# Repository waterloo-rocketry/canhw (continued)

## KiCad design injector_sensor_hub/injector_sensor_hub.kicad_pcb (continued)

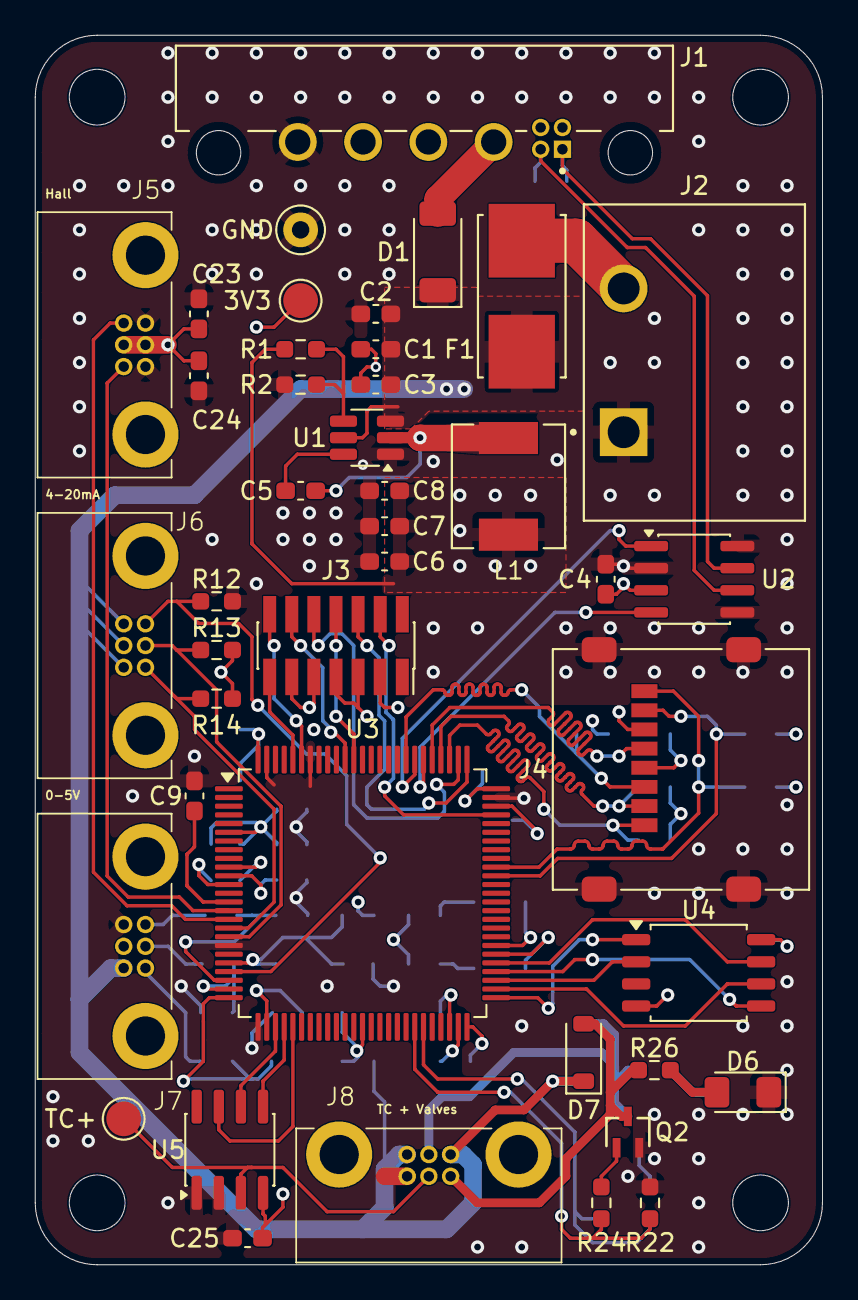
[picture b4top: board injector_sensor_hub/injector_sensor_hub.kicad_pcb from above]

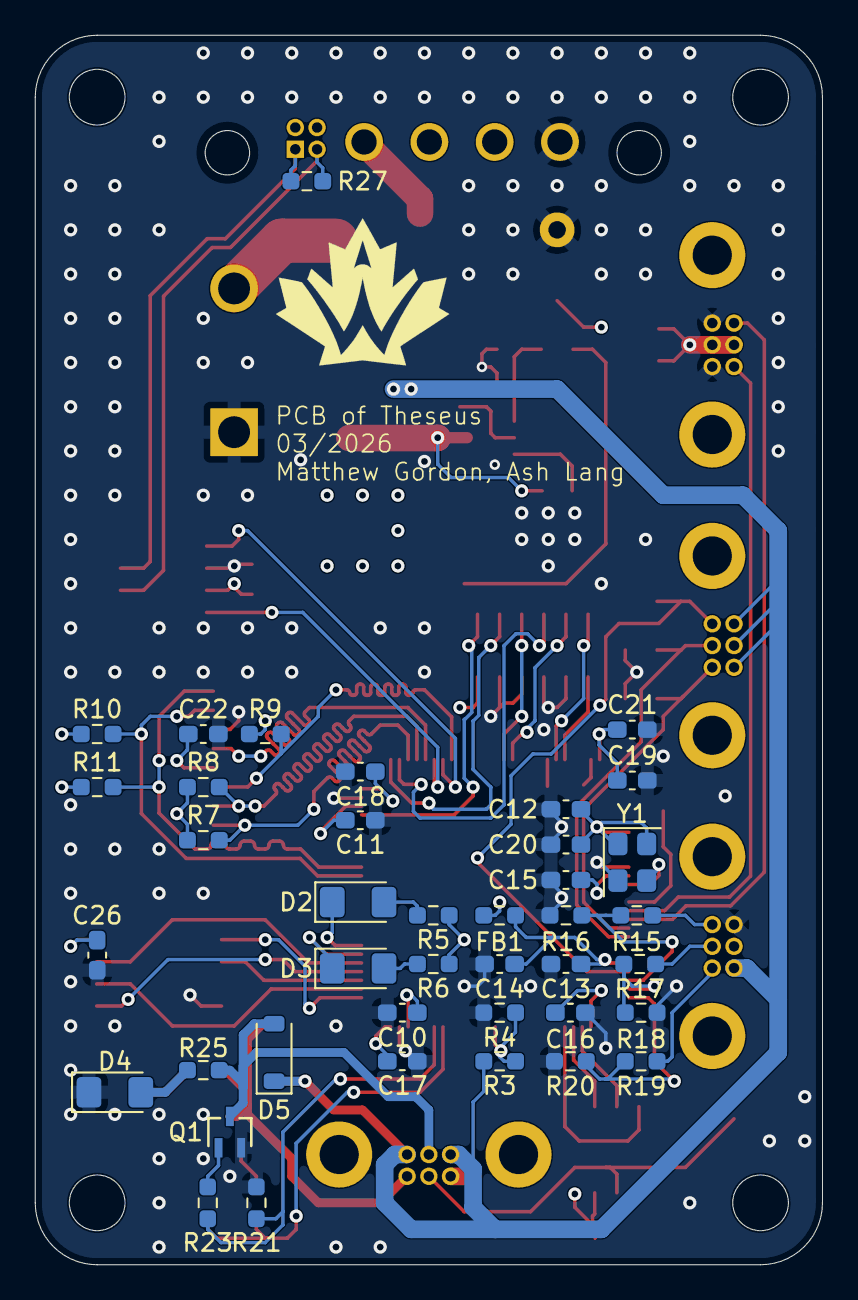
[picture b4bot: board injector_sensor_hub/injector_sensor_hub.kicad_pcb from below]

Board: 4 copper layers, 45.2 x 70.6 mm, 86 parts (40 on the bottom side), 63 nets.

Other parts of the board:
3V3: TestPoint; TestPoint_Pad_D2.0mm
GND: TestPoint; TestPoint_Keystone_5000-5004_Miniature
TC+: TC1+; TestPoint_Pad_D2.0mm

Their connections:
+3.3V: 3V3.1; also elsewhere on the board
/Valves and Sensors/TC1+: TC+.1; also elsewhere on the board
GND: GND.1; also elsewhere on the board

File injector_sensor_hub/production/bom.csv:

Designator,Footprint,Quantity,Value,LCSC Part #
3V3,TestPoint_Pad_D2.0mm,1,TestPoint,
"C1, C2, C22",0603,3,10u,
"C10, C11",0603,2,2.2u,
"C12, C13, C15, C16, C17, C18, C19, C26, C3, C5, C9",0603,11,100n,
C14,0603,1,1n,
C20,0603,1,0.01uF,
C21,0603,1,4.7u,
"C23, C24, C25, C4",0603,4,0.1u,
"C6, C7, C8",0603,3,22u,
D1,D_SOD-128,1,PMEG3030EP,
D2,1206,1,WHITE,
D3,1206,1,BLUE,
"D4, D6",1206,2,GREEN,
"D5, D7",D_SOD-123,2,CDBW140-G,
F1,FUSE_0154005.DR,1,0154005.DRL,
FB1,0603,1,PE-0603PFB121ST,
GND,TestPoint_Keystone_5000-5004_Miniature,1,TestPoint,
J1,connector_Harwin_G125-MH104M4-04AD000P,1,G125-MH104M4-04AD000P,
J2,4DB-P108-02,1,4DB-P108-02,
J3,PinSocket_2x07_P1.27mm_Vertical_SMD,1,CN4 STDC14 (Programmer),
J4,microSD_HC_Molex_47219-2001,1,Micro SD Holder 0472192001,
"J5, J6, J7, J8",connector_Harwin_G125–MG10605M4P,4,Conn_01x06_Socket,
L1,IND_SPM6530T-2R2M,1,SPM6530T-2R2M,
"Q1, Q2",SOT_12UW-7_DIO,2,DMG1012UW-7,
R1,0603,1,33.2k,
"R10, R11, R7, R8, R9",0603,5,51k,
"R12, R13, R14",0603,3,150R ±0.1%,
"R15, R17, R19",0603,3,82K,
"R16, R18, R20",0603,3,130K,
R2,0603,1,10k,
"R21, R22",0603,2,150k,
"R23, R24",0603,2,100R,
"R25, R26",0603,2,649R,
R27,0603,1,120R,
R3,0603,1,300K,
R4,0603,1,100K,
"R5, R6",0603,2,169R,
TC+,TestPoint_Pad_D2.0mm,1,TC1+,
U1,SOT-23-6_Handsoldering,1,TPS565201DDC,
U2,SOIC-8_3.9x4.9mm_P1.27mm,1,TCAN334,
U3,LQFP-100_14x14mm_P0.5mm,1,STM32H750VBTx,
U4,SOIC-8_5.3x5.3mm_P1.27mm,1,MX25L25645G,
U5,SOIC-8_3.9x4.9mm_P1.27mm,1,MAX6675,
Y1,Oscillator_SMD_Abracon_ASE-4Pin_3.2x2.5mm,1,ASE-4.000MHz-L-C-T,

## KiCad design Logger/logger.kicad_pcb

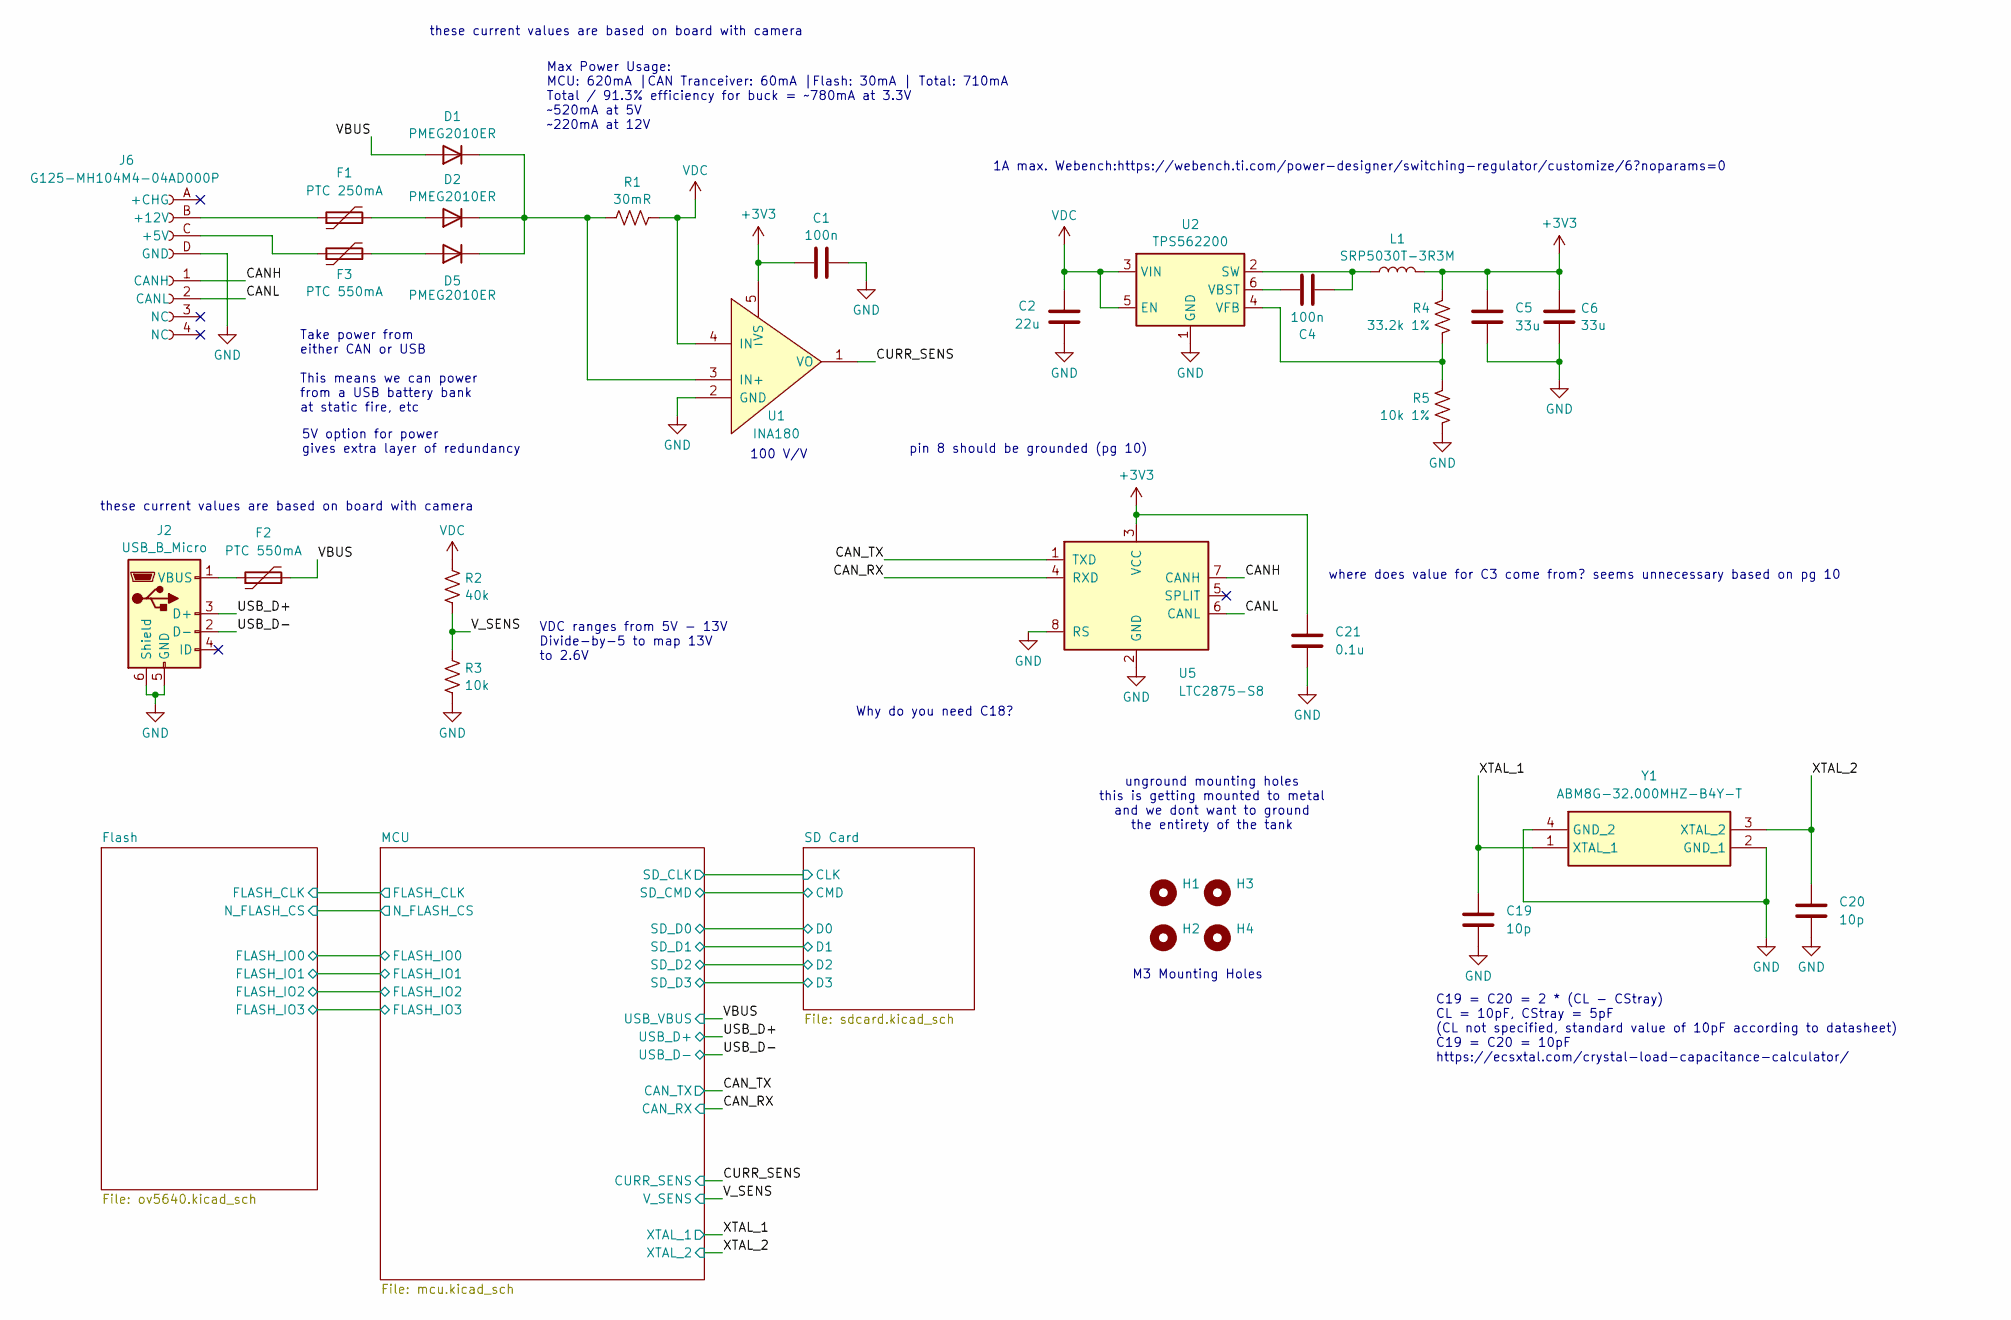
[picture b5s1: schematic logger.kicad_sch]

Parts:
C1, C4: 100n; C_0603_1608Metric_Pad1.08x0.95mm_HandSolder
C2: 22u; C_0603_1608Metric_Pad1.08x0.95mm_HandSolder
C5, C6: 33u; C_0603_1608Metric_Pad1.08x0.95mm_HandSolder
C19, C20: 10p; C_0603_1608Metric_Pad1.08x0.95mm_HandSolder
C21: 0.1u; C_0603_1608Metric_Pad1.08x0.95mm_HandSolder
D1, D2, D5: PMEG2010ER; Nexperia_CFP3_SOD-123W
F1: PTC 250mA; Fuse_1206_3216Metric_Pad1.42x1.75mm_HandSolder
F2, F3: PTC 550mA; Fuse_1206_3216Metric_Pad1.42x1.75mm_HandSolder
H1, H2, H3, H4: MountingHole; MountingHole_3.2mm_M3
J2: USB_B_Micro; USB_Micro-B_Molex_47346-0001
J6: G125-MH104M4-04AD000P; connector_Harwin_G125-MH104M4-04AD000P
L1: SRP5030T-3R3M; L_Bourns_SRP5030T
R1: 30mR; R_0603_1608Metric_Pad0.98x0.95mm_HandSolder
R2: 40k; R_0603_1608Metric_Pad0.98x0.95mm_HandSolder
R3: 10k; R_0603_1608Metric_Pad0.98x0.95mm_HandSolder
R4: 33.2k 1%; R_0603_1608Metric_Pad0.98x0.95mm_HandSolder
R5: 10k 1%; R_0603_1608Metric_Pad0.98x0.95mm_HandSolder
U1: INA180; SOT-23-5_HandSoldering
U2: TPS562200; SOT-23-6_Handsoldering
U5: LTC2875-S8; SOIC-8_3.9x4.9mm_P1.27mm
Y1: ABM8G-32.000MHZ-B4Y-T; Crystal_SMD_Abracon_ABM8G-4Pin_3.2x2.5mm; Manufacturer_Part_Number ABM8G-32.000MHZ-B4Y-T

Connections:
+3V3: C1.1, C5.1, C6.1, C21.1, L1.2, R4.1, U1.5 (VS), U5.3 (VCC); also elsewhere on the board
/CANH: J6.1 (CANH), U5.7 (CANH)
/CANL: J6.2 (CANL), U5.6 (CANL)
/CAN_RX: U5.4 (RXD); also elsewhere on the board
/CAN_TX: U5.1 (TXD); also elsewhere on the board
/CURR_SENS: U1.1 (VO); also elsewhere on the board
/USB_D+: J2.3 (D+); also elsewhere on the board
/USB_D-: J2.2 (D-); also elsewhere on the board
/VBUS: D1.2 (A), F2.2; also elsewhere on the board
/V_SENS: R2.2, R3.1; also elsewhere on the board
/XTAL_1: C19.1, Y1.1 (XTAL_1); also elsewhere on the board
/XTAL_2: C20.1, Y1.3 (XTAL_2); also elsewhere on the board
GND: C1.2, C2.2, C5.2, C6.2, C19.2, C20.2, C21.2, J2.5 (GND), J2.6 (Shield), J6.D (GND), R3.2, R5.2, U1.2 (GND), U2.1 (GND), U5.2 (GND), U5.8 (RS), Y1.2 (GND_1), Y1.4 (GND_2); also elsewhere on the board
unnamed: D1.1 (K), D2.1 (K), D5.1 (K), R1.1, U1.3 (IN+)
unnamed: D2.2 (A), F1.2
unnamed: D5.2 (A), F3.2
unnamed: F2.1, J2.1 (VBUS)
unnamed: F3.1, J6.C (+5V)
unnamed: F1.1, J6.B (+12V)
unnamed: C4.2, L1.1, U2.2 (SW)
unnamed: C4.1, U2.6 (VBST)
unnamed: R4.2, R5.1, U2.4 (VFB)
VDC: C2.1, R1.2, R2.1, U1.4 (IN-), U2.3 (VIN), U2.5 (EN)

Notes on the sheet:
unground mounting holes this is getting mounted to metal and we dont want to ground the entirety of the tank
5V option for power gives extra layer of redundancy
pin 8 should be grounded (pg 10)
C19 = C20 = 2 * (CL - CStray) CL = 10pF, CStray = 5pF (CL not specified, standard value of 10pF according to datasheet) C19 = C20 = 10pF https://ecsxtal.com/crystal-load-capacitance-calculator/
VDC ranges from 5V - 13V Divide-by-5 to map 13V to 2.6V
these current values are based on board with camera
100 V/V
Why do you need C18?
1A max. Webench:https://webench.ti.com/power-designer/switching-regulator/customize/6?noparams=0
M3 Mounting Holes
Max Power Usage: MCU: 620mA |CAN Tranceiver: 60mA |Flash: 30mA | Total: 710mA Total / 91.3% efficiency for buck = ~780mA at 3.3V ~520mA at 5V ~220mA at 12V
where does value for C3 come from? seems unnecessary based on pg 10
Take power from either CAN or USB This means we can power from a USB battery bank at static fire, etc

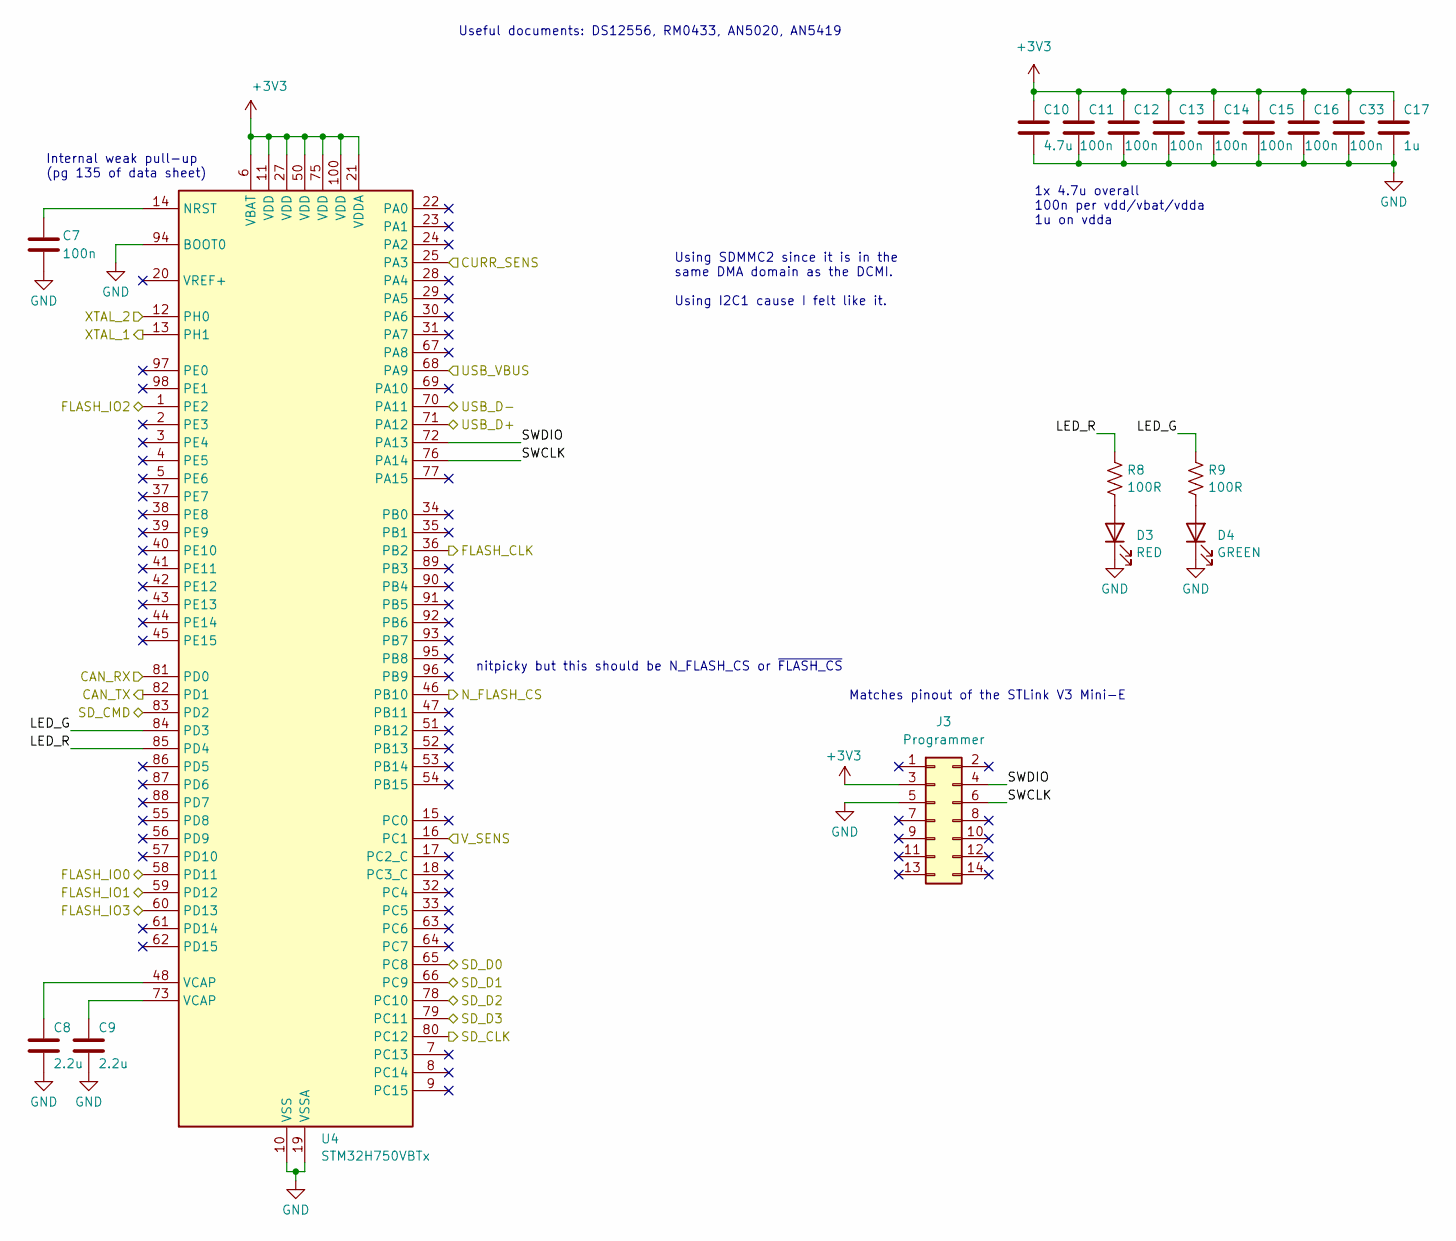
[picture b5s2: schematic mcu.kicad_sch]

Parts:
C7, C11, C12, C13, C14, C15, C16, C33: 100n; C_0603_1608Metric_Pad1.08x0.95mm_HandSolder
C8, C9: 2.2u; C_0603_1608Metric_Pad1.08x0.95mm_HandSolder
C10: 4.7u; C_0603_1608Metric_Pad1.08x0.95mm_HandSolder
C17: 1u; C_0603_1608Metric_Pad1.08x0.95mm_HandSolder
D3: RED; LED_1206_3216Metric_Pad1.42x1.75mm_HandSolder
D4: GREEN; LED_1206_3216Metric_Pad1.42x1.75mm_HandSolder
J3: Programmer; PinHeader_2x07_P1.27mm_Vertical_SMD
R8, R9: 100R; R_0603_1608Metric_Pad0.98x0.95mm_HandSolder
U4: STM32H750VBTx; LQFP-100_14x14mm_P0.5mm

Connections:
+3V3: C10.1, C11.1, C12.1, C13.1, C14.1, C15.1, C16.1, C17.1, C33.1, J3.3, U4.6 (VBAT), U4.11 (VDD), U4.21 (VDDA), U4.27 (VDD), U4.50 (VDD), U4.75 (VDD), U4.100 (VDD); also elsewhere on the board
/CAN_RX: U4.81 (PD0); also elsewhere on the board
/CAN_TX: U4.82 (PD1); also elsewhere on the board
/CURR_SENS: U4.25 (PA3); also elsewhere on the board
/Flash/FLASH_CLK: U4.36 (PB2); also elsewhere on the board
/Flash/FLASH_IO0: U4.58 (PD11); also elsewhere on the board
/Flash/FLASH_IO1: U4.59 (PD12); also elsewhere on the board
/Flash/FLASH_IO2: U4.1 (PE2); also elsewhere on the board
/Flash/FLASH_IO3: U4.60 (PD13); also elsewhere on the board
/Flash/N_FLASH_CS: U4.46 (PB10); also elsewhere on the board
/MCU/LED_G: R9.1, U4.84 (PD3)
/MCU/LED_R: R8.1, U4.85 (PD4)
/MCU/SD_CLK: U4.80 (PC12); also elsewhere on the board
/MCU/SD_CMD: U4.83 (PD2); also elsewhere on the board
/MCU/SD_D0: U4.65 (PC8); also elsewhere on the board
/MCU/SD_D1: U4.66 (PC9); also elsewhere on the board
/MCU/SD_D2: U4.78 (PC10); also elsewhere on the board
/MCU/SD_D3: U4.79 (PC11); also elsewhere on the board
/MCU/SWCLK: J3.6, U4.76 (PA14)
/MCU/SWDIO: J3.4, U4.72 (PA13)
/USB_D+: U4.71 (PA12); also elsewhere on the board
/USB_D-: U4.70 (PA11); also elsewhere on the board
/VBUS: U4.68 (PA9); also elsewhere on the board
/V_SENS: U4.16 (PC1); also elsewhere on the board
/XTAL_1: U4.13 (PH1); also elsewhere on the board
/XTAL_2: U4.12 (PH0); also elsewhere on the board
GND: C7.2, C8.2, C9.2, C10.2, C11.2, C12.2, C13.2, C14.2, C15.2, C16.2, C17.2, C33.2, D3.1 (K), D4.1 (K), J3.5, U4.10 (VSS), U4.19 (VSSA), U4.26 (VSS), U4.49 (VSS), U4.74 (VSS), U4.94 (BOOT0), U4.99 (VSS); also elsewhere on the board
unnamed: C8.1, U4.48 (VCAP)
unnamed: C9.1, U4.73 (VCAP)
unnamed: D3.2 (A), R8.2
unnamed: D4.2 (A), R9.2
unnamed: C7.1, U4.14 (NRST)

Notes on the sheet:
nitpicky but this should be N_FLASH_CS or ~{FLASH_CS}
1x 4.7u overall 100n per vdd/vbat/vdda 1u on vdda
Matches pinout of the STLink V3 Mini-E
Useful documents: DS12556, RM0433, AN5020, AN5419
Using SDMMC2 since it is in the same DMA domain as the DCMI. Using I2C1 cause I felt like it.
Internal weak pull-up (pg 135 of data sheet)

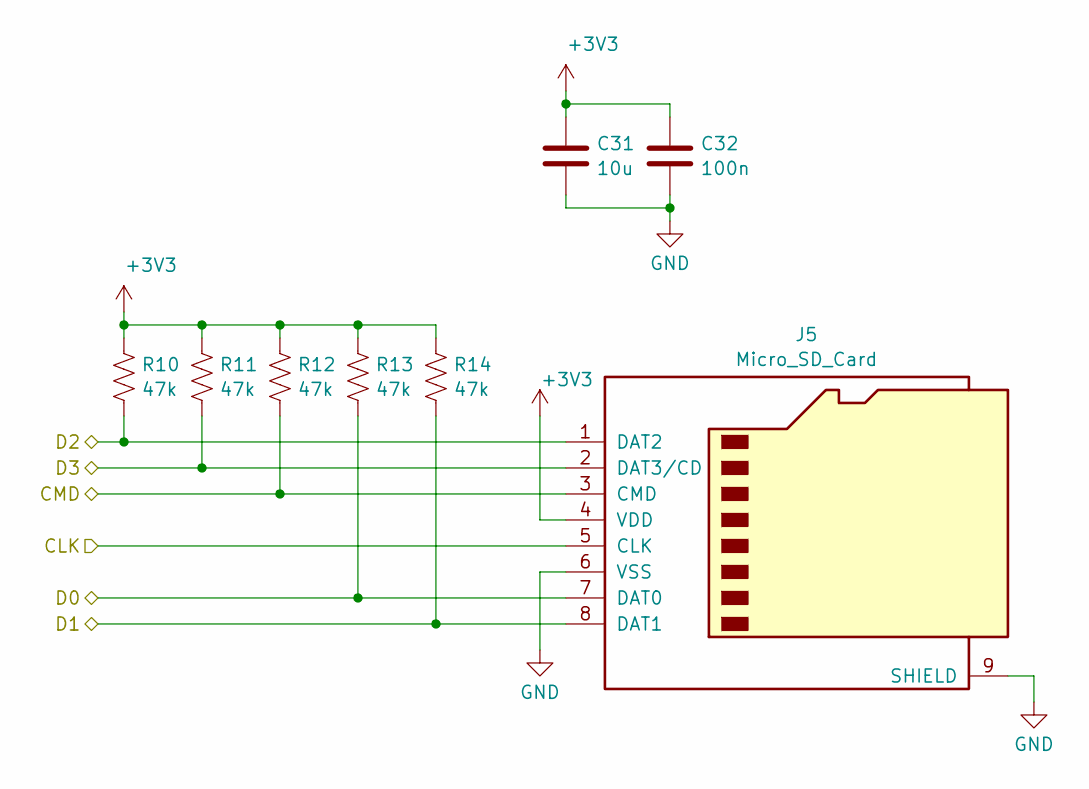
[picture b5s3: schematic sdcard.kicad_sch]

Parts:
C31: 10u; C_0603_1608Metric_Pad1.08x0.95mm_HandSolder
C32: 100n; C_0603_1608Metric_Pad1.08x0.95mm_HandSolder
J5: Micro_SD_Card; microSD_Molex_WM6698CT-ND
R10, R11, R12, R13, R14: 47k; R_0603_1608Metric_Pad0.98x0.95mm_HandSolder

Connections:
+3V3: C31.1, C32.1, J5.4 (VDD), R10.1, R11.1, R12.1, R13.1, R14.1; also elsewhere on the board
/MCU/SD_CLK: J5.5 (CLK); also elsewhere on the board
/MCU/SD_CMD: J5.3 (CMD), R12.2; also elsewhere on the board
/MCU/SD_D0: J5.7 (DAT0), R13.2; also elsewhere on the board
/MCU/SD_D1: J5.8 (DAT1), R14.2; also elsewhere on the board
/MCU/SD_D2: J5.1 (DAT2), R10.2; also elsewhere on the board
/MCU/SD_D3: J5.2 (DAT3/CD), R11.2; also elsewhere on the board
GND: C31.2, C32.2, J5.6 (VSS), J5.9 (SHIELD); also elsewhere on the board

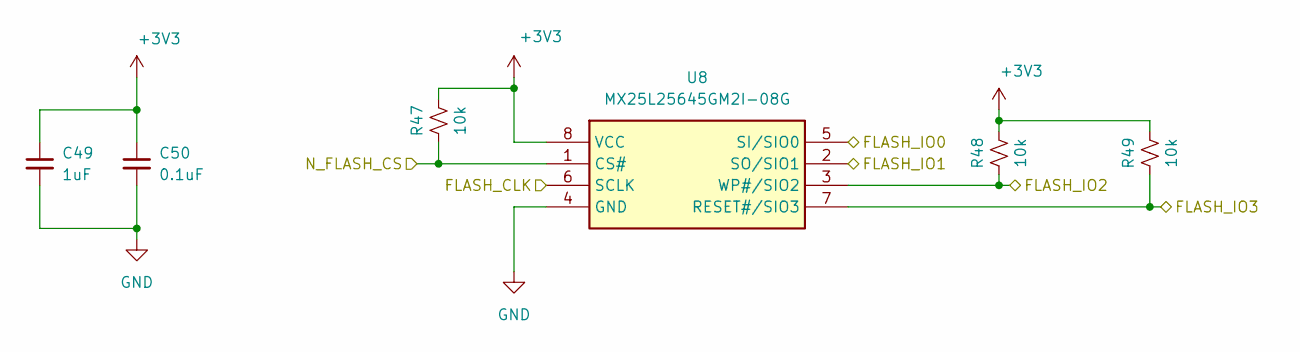
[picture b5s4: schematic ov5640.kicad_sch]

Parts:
C49: 1uF; C_0603_1608Metric_Pad1.08x0.95mm_HandSolder; LCSC Part # C49678
C50: 0.1uF; C_0603_1608Metric_Pad1.08x0.95mm_HandSolder; LCSC Part # C49678
R47, R48, R49: 10k; R_0603_1608Metric_Pad0.98x0.95mm_HandSolder; LCSC Part # C17414
U8: MX25L25645GM2I-08G; SOIC-8_5.3x5.3mm_P1.27mm; Mouser Part Number 95-25L25645GM2I0TR

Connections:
+3V3: C49.1, C50.1, R47.1, R48.1, R49.1, U8.8 (VCC); also elsewhere on the board
/Flash/FLASH_CLK: U8.6 (SCLK); also elsewhere on the board
/Flash/FLASH_IO0: U8.5 (SI/SIO0); also elsewhere on the board
/Flash/FLASH_IO1: U8.2 (SO/SIO1); also elsewhere on the board
/Flash/FLASH_IO2: R48.2, U8.3 (WP#/SIO2); also elsewhere on the board
/Flash/FLASH_IO3: R49.2, U8.7 (RESET#/SIO3); also elsewhere on the board
/Flash/N_FLASH_CS: R47.2, U8.1 (CS#); also elsewhere on the board
GND: C49.2, C50.2, U8.4 (GND); also elsewhere on the board

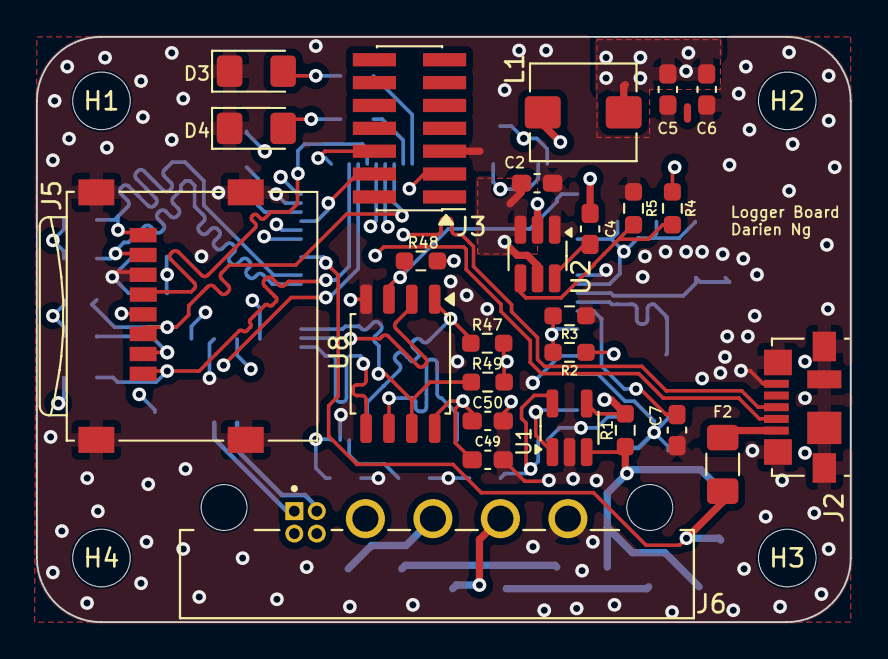
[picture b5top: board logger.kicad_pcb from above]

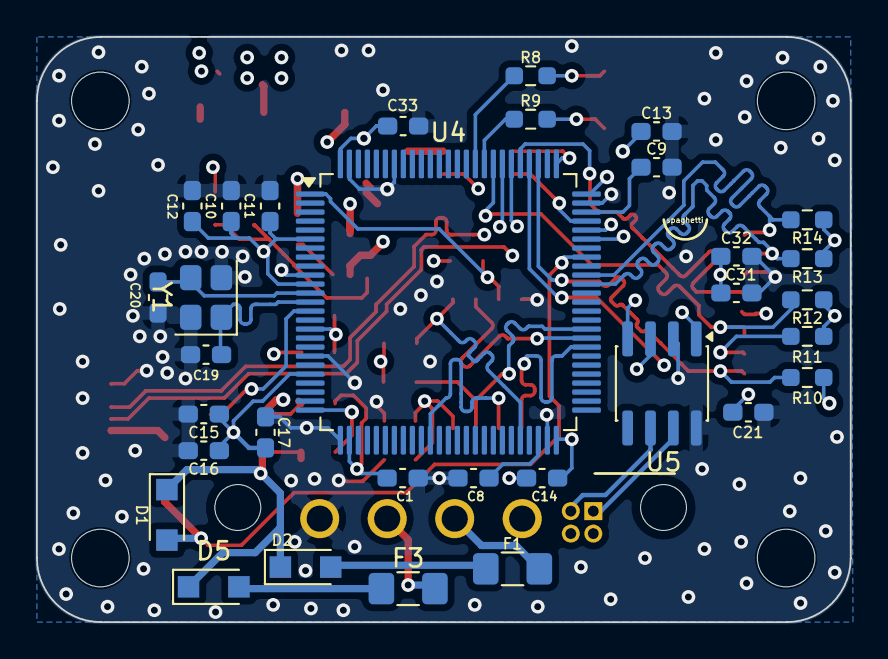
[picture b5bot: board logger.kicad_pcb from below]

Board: 4 copper layers, 45.2 x 32.5 mm, 62 parts (32 on the bottom side), 44 nets.

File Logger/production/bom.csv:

Designator,Footprint,Quantity,Value,LCSC Part #
"C1, C11, C12, C13, C14, C15, C16, C32, C33, C4, C7",0603,11,100n,
C10,0603,1,4.7u,
C17,0603,1,1u,
"C19, C20",0603,2,10p,
C2,0603,1,22u,
C21,0603,1,0.1u,
C31,0603,1,10u,
C49,0603,1,1uF,C49678
"C5, C6",0603,2,33u,
C50,0603,1,0.1uF,C49678
"C8, C9",0603,2,2.2u,
"D1, D2, D5",Nexperia_CFP3_SOD-123W,3,PMEG2010ER,
D3,1206,1,RED,
D4,1206,1,GREEN,
F1,1206,1,PTC 250mA,
"F2, F3",1206,2,PTC 550mA,
J2,USB_Micro-B_Molex_47346-0001,1,USB_B_Micro,
J3,PinHeader_2x07_P1.27mm_Vertical_SMD,1,Programmer,
J5,microSD_Molex_WM6698CT-ND,1,Micro_SD_Card,
J6,connector_Harwin_G125-MH104M4-04AD000P,1,G125-MH104M4-04AD000P,
L1,L_Bourns_SRP5030T,1,SRP5030T-3R3M,
R1,0603,1,30mR,
"R10, R11, R12, R13, R14",0603,5,47k,
R2,0603,1,40k,
R3,0603,1,10k,
R4,0603,1,33.2k 1%,
"R47, R48, R49",0603,3,10k,C17414
R5,0603,1,10k 1%,
"R8, R9",0603,2,100R,
U1,SOT-23-5_HandSoldering,1,INA180,
U2,SOT-23-6_Handsoldering,1,TPS562200,
U4,LQFP-100_14x14mm_P0.5mm,1,STM32H750VBTx,
U5,SOIC-8_3.9x4.9mm_P1.27mm,1,LTC2875-S8,
U8,SOIC-8_5.3x5.3mm_P1.27mm,1,MX25L25645GM2I-08G,
Y1,Crystal_SMD_Abracon_ABM8G-4Pin_3.2x2.5mm,1,ABM8G-32.000MHZ-B4Y-T,

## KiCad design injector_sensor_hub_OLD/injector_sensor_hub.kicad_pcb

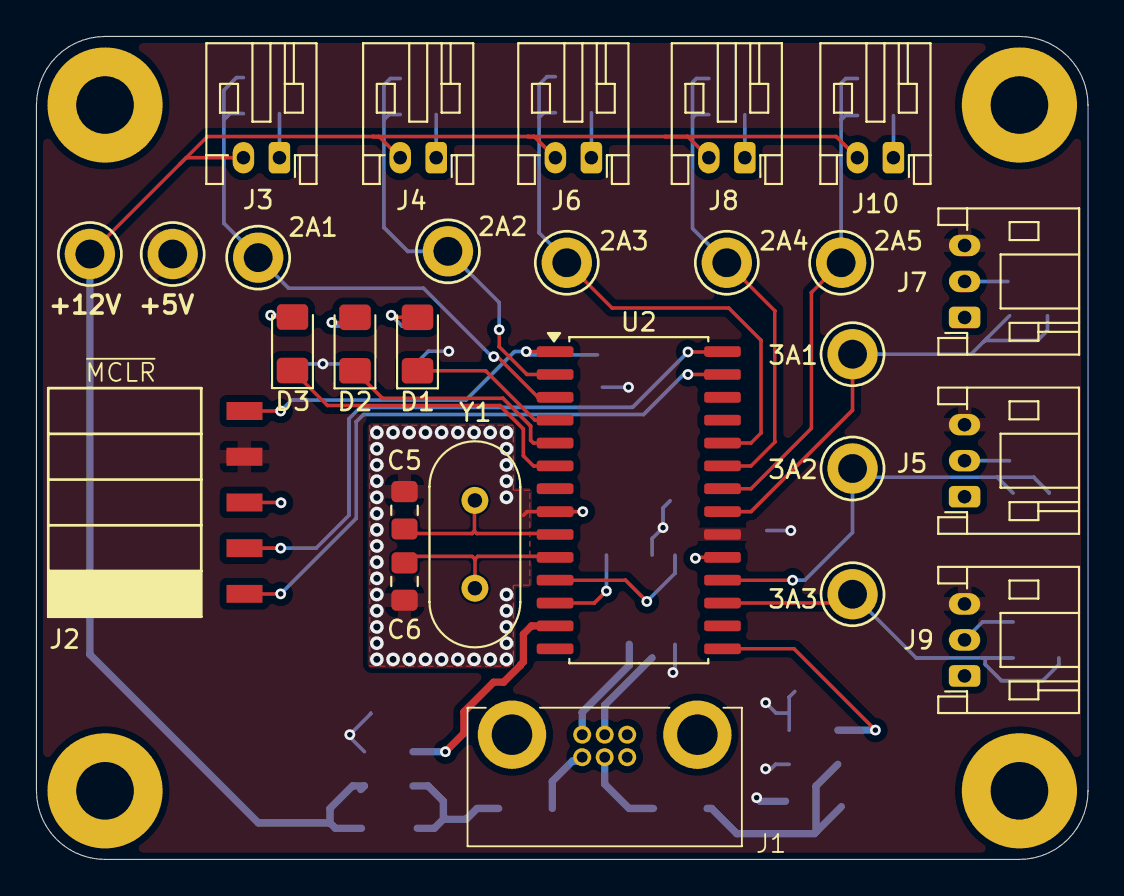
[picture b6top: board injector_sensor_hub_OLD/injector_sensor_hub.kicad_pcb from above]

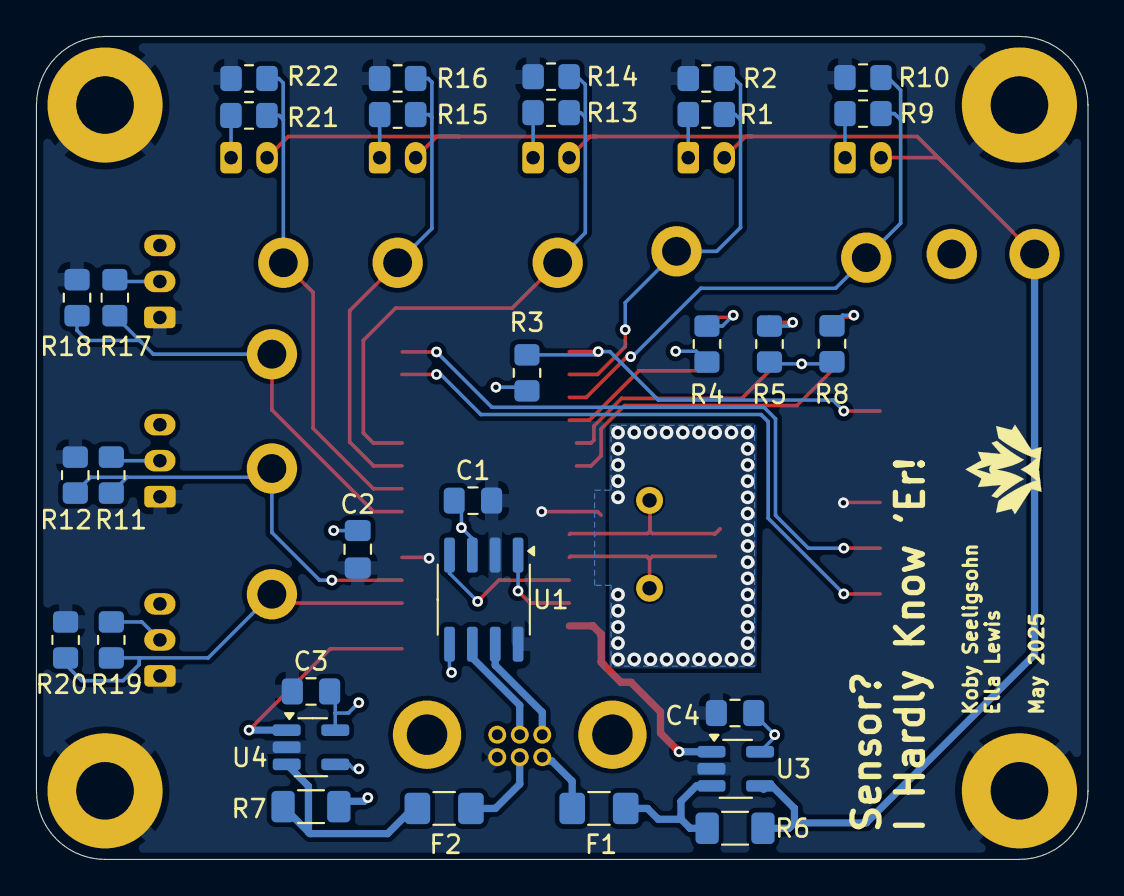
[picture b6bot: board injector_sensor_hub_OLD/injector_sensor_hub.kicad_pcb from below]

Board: 2 copper layers, 58.4 x 45.7 mm, 62 parts (31 on the bottom side), 40 nets.

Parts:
2A1, 2A2, 2A3, 2A4, 2A5, 3A1, 3A2, 3A3: TestPoint; TestPoint_Keystone_5005-5009_Compact
C1: 10uF; C_0805_2012Metric_Pad1.18x1.45mm_HandSolder
C2, C3: 0.1uF; C_0805_2012Metric_Pad1.18x1.45mm_HandSolder
C4: 0.1 uF; C_0805_2012Metric_Pad1.18x1.45mm_HandSolder
C5, C6: 27pF; C_0805_2012Metric_Pad1.18x1.45mm_HandSolder
D1: BLUE; LED_1206_3216Metric_Pad1.42x1.75mm_HandSolder
D2: WHITE; LED_1206_3216Metric_Pad1.42x1.75mm_HandSolder
D3: RED; LED_1206_3216Metric_Pad1.42x1.75mm_HandSolder
F1, F2: 350mA; Fuse_1206_3216Metric_Pad1.42x1.75mm_HandSolder
H1, H2: +5V; MountingHole_3.2mm_M3_Pad
H3, H4: MountingHole_Pad; MountingHole_3.2mm_M3_Pad
J1: CAN_Connector; connector_Harwin_G125–MG10605M4P
J2: Programming Header; PinSocket_5x2.54_SMD_90deg_952-3198-1-ND
J3, J4, J6, J8, J10: Conn_01x02_Female-Connector; JST_PH_S2B-PH-K_1x02_P2.00mm_Horizontal
J5, J7, J9: Conn_01x03_Female; JST_PH_S3B-PH-K_1x03_P2.00mm_Horizontal
R1, R2, R9, R10, R11, R12, R13, R14, R15, R16, R17, R18, R19, R20, R21, R22: TBD; R_0805_2012Metric_Pad1.20x1.40mm_HandSolder
R3: 10K; R_0805_2012Metric_Pad1.20x1.40mm_HandSolder
R4: 180R; R_0805_2012Metric_Pad1.20x1.40mm_HandSolder
R5: 220R; R_0805_2012Metric_Pad1.20x1.40mm_HandSolder
R6, R7: 130mR; R_1206_3216Metric_Pad1.30x1.75mm_HandSolder
R8: 300R; R_0805_2012Metric_Pad1.20x1.40mm_HandSolder
TP1: TP_5V; TestPoint_Keystone_5005-5009_Compact
TP4: TP_12V; TestPoint_Keystone_5005-5009_Compact
U1: MCP2562; SOIC-8_3.9x4.9mm_P1.27mm
U2: PIC18F26K83; SOIC-28W_7.5x17.9mm_P1.27mm
U3, U4: INA180; SOT-23-5_HandSoldering
Y1: Crystal; Crystal_HC49-4H_Vertical

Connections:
+5V: C1.1, C2.2, C3.2, C4.2, J2.4, J5.3, J7.3, J9.3, R3.1, R4.2, R5.2, R7.1, R8.2, TP1.1, U1.3 (VDD), U1.5 (VIO), U2.20 (VDD), U3.5 (VS), U4.4 (IN-), U4.5 (VS)
+12V: J3.2, J4.2, J6.2, J8.2, J10.2, R6.1, TP4.1, U3.4 (IN-)
/5V_CURR: U2.15 (RC4), U4.1 (VO)
/12V_CURR: U2.13 (RC2), U3.1 (VO)
/Analog Sensor Input/2ANALOG_1: 2A1.1, R9.2, R10.1, U2.3 (RA1)
/Analog Sensor Input/2ANALOG_2: 2A2.1, R1.2, R2.1, U2.2 (RA0)
/Analog Sensor Input/2ANALOG_3: 2A3.1, R13.2, R14.1, U2.24 (RB3)
/Analog Sensor Input/2ANALOG_4: 2A4.1, R15.2, R16.1, U2.23 (RB2)
/Analog Sensor Input/2ANALOG_5: 2A5.1, R21.2, R22.1, U2.22 (RB1)
/Analog Sensor Input/3ANALOG_1: 3A1.1, R17.2, R18.1, U2.21 (RB0)
/Analog Sensor Input/3ANALOG_2: 3A2.1, R11.2, R12.1, U2.18 (RC7)
/Analog Sensor Input/3ANALOG_3: 3A3.1, R19.2, R20.1, U2.17 (RC6)
/MCU/CAN_RX: U1.4 (RXD), U2.11 (RC0)
/MCU/CAN_TX: U1.1 (TXD), U2.12 (RC1)
/MCU/ICSPCLK: J2.1, U2.27 (RB6/ICSPCLK)
/MCU/ICSPDAT: J2.2, U2.28 (RB7/ICSPDAT)
/MCU/LED_GREEN: D1.1 (K), U2.4 (RA2)
/MCU/LED_RED: D3.1 (K), U2.6 (RA4)
/MCU/LED_WHITE: D2.1 (K), U2.5 (RA3)
/MCU/OSC1: C5.1, U2.9 (RA7/OSC1), Y1.1
/MCU/OSC2: C6.1, U2.10 (RA6/OSC2), Y1.2
/MCU/~MCLR: J2.5, R3.2, U2.1 (~MCLR)
CANH: J1.3, U1.7 (CANH)
CANL: J1.2, U1.6 (CANL)
GND: C1.2, C2.1, C3.1, C4.1, C5.2, C6.2, H1.1, H2.1, H3.1, H4.1, J1.4, J2.3, J5.1, J7.1, J9.1, R2.2, R10.2, R12.2, R14.2, R16.2, R18.2, R20.2, R22.2, U1.2 (VSS), U1.8 (STBY), U2.8 (VSS), U2.19 (VSS), U3.2 (GND), U4.2 (GND)
unnamed: D1.2 (A), R4.1
unnamed: D2.2 (A), R5.1
unnamed: D3.2 (A), R8.1
unnamed: F2.2, J1.5
unnamed: F1.2, J1.6
unnamed: J3.1, R9.1
unnamed: J4.1, R1.1
unnamed: J5.2, R11.1
unnamed: J6.1, R13.1
unnamed: J7.2, R17.1
unnamed: J8.1, R15.1
unnamed: J9.2, R19.1
unnamed: J10.1, R21.1
unnamed: F1.1, R6.2, U3.3 (IN+)
unnamed: F2.1, R7.2, U4.3 (IN+)
